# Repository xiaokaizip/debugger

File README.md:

#### 调试器电路

##### 主控（stm32f401rct6）

##### 屏幕（tft屏）

##### 闪存（W25Q32JVSSIQ）

##### 触摸功能（XPT2946）

##### 按键

#### 代码

##### tft屏驱动

- tft屏幕与主控使用spi通讯，然后为了提高屏幕的刷新率，我使用了DMA进行数据的传输。
- tft屏幕的配置更多还是使用网上的库，方便直接。
- 学会更好的使用DMA

##### 触摸功能

- 触摸的功能相对于tft屏幕的驱动来说，是比较好写，但是要完善也还不是很容易，它的功能还需再来研究。

==这两部分可以借鉴老朱的代码（手动狗头），养成写注释的习惯，等到功能写出来再来整理到readme中==

# Debegger

## 代码的设计

### tft屏幕显示

- spi的配置，如下图：（然后再开启个DMA就可以了）

- 屏幕的初始化还是使用普通的方法对其进行初始化（那些初始化的指令还没去了解）。

- 首先是屏幕的设计，目前的想法是，先将一整个屏幕的数据处理完，再使用DMA传输一次性完成传输。（已完成）

- 先将要处理的像素点存储到数组中

~~~c
volatile unsigned char lcd_buffer[128 * 160 * 2] = {0};

~~~

然后直接使用DMA将数据传输到ftf屏中

~~~c
    HAL_SPI_Transmit_DMA(&hspi3, (uint8_t *) lcd_buffer, 128 * 160 * 2);
~~~

- 然后就是对数组的处理了，每一个数组对应tft屏中的一个像素点，所以在处理时，只需将对应的像素点输入对应的颜色指令即可。
  - 在此代码中对应的字符大小为12*6，即宽为6像素，高为12像素。
  - 处理字符时，先从行开始处理的，依次向下处理。
  - 至于其他的方框，就是直接抄袭老朱的代码。（还需待我看懂）

### 串口数据的处理

##### 配置

- 首先是串口的接口，在本调试器中，使用的串口是USART1和UART4

  - usart1：typeC接口，具有usb2ttl芯片

    PA10->RX

    PA9->TX

  - uart4：使用的是gh1.25的接口。

    PC10->TX

    PC11->RX

- 发送数据的时候，还是用了轮询模式。接收数据的时候，使用的是中断模式。

##### 数据类型转换

- 串口传输的是8位的数，所以如果要传输更长的数据类型，需要转换一下数据的类型。在本例程中要传输的是float的数据，所以float和unsigned short 两种类型的数据相互转换。

- 将float转换为unsigned short

  ~~~c
  unsigned short FloatToInt16(float data0)
  ~~~

- 将unsigned short转换为float

  ~~~c
  float Int16ToFloat(unsigned short data0)
  
  ~~~

##### 传输格式

- 目前暂定传输和接收4个float类型数据（这四个数据分别为data1、data2、data3、data4）。使用长度为11的数据。

| 0    | 1    | 2    | 3    | 4    | 5    | 6    | 7    | 8    | 9      | 10   |
| ---- | ---- | ---- | ---- | ---- | ---- | ---- | ---- | ---- | ------ | ---- |
| 0xff | 高位 | 低位 | 高位 | 低位 | 高位 | 低位 | 高位 | 低位 | 校准位 | 0xff |

- 第零位为起始位，指定为0xff，低十位为结束位，指定为0xff。
- 第1位是data1的高8位，第2位是data1低8位。其他的以此类推。
- 第9位是校准位，其实起这个名字可能不太合适，这一位的作用就是用来表示接收了多少个有效数据（非零数据）

## 图形界面的设计

### 现阶段流程图

- 在每一个界面中都有一个TurnBuck选项（除了main_forms界面），按下此界面就会回到上一个界面。这个回调的方法不知是要不要使用链表（有待思考）。

- 图形界面只是使用了按键（Button）以及标签（label）来设计的简易界面。Key1用来移动光标，Key2用来确定进入相依的界面，并使用回调函数还进行初始化，配合链表可能会有更好的效果。

### 设计思路

- key1为选择键，当key1按下时key_Select_flag++；同时相应的button将会高亮表示被选择到。
- 当按下key2时，为确定按键。此时key_Verify_flag=1。此时将会根据key_Select_flag的值调用 相应 的回调函数 进入相应的界面。然后key_Verify_flag被重新置零。
- 此流程是相对较简单的。后面的想法是使用链表来实现界面的切换 。

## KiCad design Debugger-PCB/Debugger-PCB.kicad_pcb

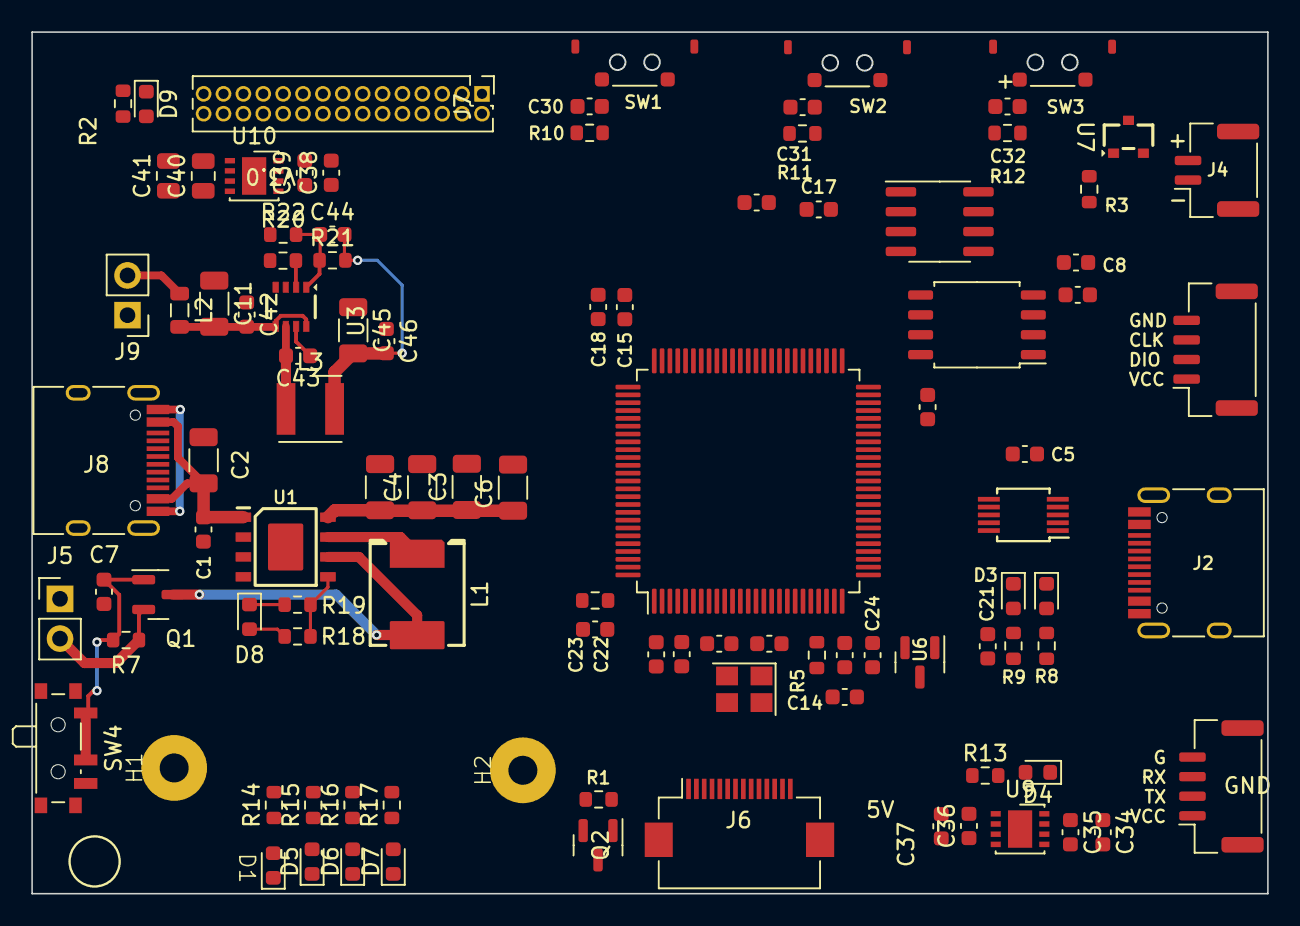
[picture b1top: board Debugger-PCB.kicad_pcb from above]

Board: 2 copper layers, 78.9 x 55.0 mm, 102 parts (0 on the bottom side), 86 nets.

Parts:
C1, C5, C7, C8, C9, C14, C17, C18, C19, C20, C21, C22, C23, C24, C30, C31, C32, C33, C35, C37, C39, C42: 100n; C_0603_1608Metric
C2: 10u; C_1206_3216Metric
C3, C4, C6, C10: 22u; C_1206_3216Metric
C11: 106 1206; C_1206_3216Metric
C12, C13: 12p; C_0603_1608Metric
C15, C16: 2.2u; C_0603_1608Metric
C34, C36, C38: 4.7u; C_0603_1608Metric
C40: 4.7u; C_0805_2012Metric
C41: 100n; C_0805_2012Metric
C43: 103; C_0603_1608Metric
C44: 101; C_0603_1608Metric
C45: 22uf 0603; C_1206_3216Metric
C46: 104; C_0603_1608Metric
D1, D5, D6, D7, D8: LED_0603_1608Metric
D2, D3, D4, D9: LED; LED_0603_1608Metric
H1, H2: MountingHole; mo
J1, J3: Conn_01x04; JST_GH_SM04B-GHS-TB_1x04-1MP_P1.25mm_Horizontal
J2, J8: USB_C_Receptacle_USB2.0; USB_C_Receptacle_HRO_TYPE-C-31-M-12
J4: Conn_01x02; JST_GH_SM02B-GHS-TB_1x02-1MP_P1.25mm_Horizontal
J5, J9: Conn_01x02; PinHeader_1x02_P2.54mm_Vertical
J6: Conn_01x14; Hirose_FH12-14S-0.5SH_1x14-1MP_P0.50mm_Horizontal
J7: axt430124; PinHeader_2x15_P1.27mm_Vertical
L1: 1u; MC-0630
L2: 600r; L_0805_2012Metric
L3: 2.2uh; L_Wurth_WE-LQSH-4020
Q1: AO3407; SOT-23
Q2: SI2301; SOT-23
R1, R6: 10K; R_0603_1608Metric
R2, R13: 1K; R_0603_1608Metric
R3: 120; R_0603_1608Metric
R5, R7, R14, R15, R16, R17, R18, R19: 10k; R_0603_1608Metric
R8, R9, R10, R11, R12: 1k; R_0603_1608Metric
R20: 200K; R_0603_1608Metric
R21: 220K; R_0603_1608Metric
R22: 30k; R_0603_1608Metric
SW1, SW2, SW3: SW_Push; button
SW4: SW_SPDT; SW_SPDT_PCM12
U1: IP5306; SOP-8EP_3949
U2: CH340E; MSOP-10_3x3mm_P0.5mm
U3: SY8303; SOT-23-8
U4: TJA1051T-3; SOIC-8_3.9x4.9mm_P1.27mm
U5: STM32F407VETx; LQFP-100_14x14mm_P0.5mm
U6: REF3030; SOT-23
U7: pesd1can; SOT-23
U8: W25Q32JVSS; SOIC-8_5.23x5.23mm_P1.27mm
U9, U10: DFN-8-1EP_3x3mm_P0.65mm_EP1.55x2.4mm
Y1: 12M; Crystal_SMD_3225-4Pin_3.2x2.5mm

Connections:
+5V: C3.1, C4.1, C6.1, C9.1, C10.1, C34.2, C35.2, C38.2, C39.2, C44.2, C45.2, C46.2, J2.A4 (VBUS), J2.A9 (VBUS), J2.B4 (VBUS), J2.B9 (VBUS), J7.30, L3.2, R21.2, U1.8 (VOUT), U4.3 (VCC), U9.5 (EN), U9.8 (IN), U10.5 (EN), U10.8 (IN)
/Flash/SPI2_CS: U5.51 (PB12), U8.1 (~CS)
/Flash/SPI2_MISO: U5.53 (PB14), U8.2 (DO(IO1))
/Flash/SPI2_MOSI: U5.54 (PB15), U8.5 (DI(IO0))
/Flash/SPI2_SCK: U5.52 (PB13), U8.6 (CLK)
/Key&LED/KEY1: C30.1, J6.8, R10.2, SW1.2, U5.37 (PB2)
/Key&LED/KEY2: C31.1, J6.9, R11.2, SW2.2, U5.36 (PB1)
/Key&LED/KEY3: C32.1, J6.10, R12.2, SW3.2, U5.35 (PB0)
/Key&LED/LED1: D2.1 (K), U5.39 (PE8)
/Key&LED/LED2: D3.1 (K), U5.38 (PE7)
/MCU/ADC1_IN0: J7.25, U5.23 (PA0)
/MCU/ADC1_IN1: J7.24, U5.24 (PA1)
/MCU/ADC1_IN11: J7.29, U5.16 (PC1)
/MCU/ADC1_IN12: J7.28, U5.17 (PC2)
/MCU/ADC1_IN13: J7.27, U5.18 (PC3)
/MCU/ADC1_IN14: J7.26, U5.33 (PC4)
/MCU/CAN_RX: U4.4 (RXD), U5.70 (PA11)
/MCU/CAN_TX: U4.1 (TXD), U5.71 (PA12)
/MCU/I2C3_SCL: J7.13, U5.67 (PA8)
/MCU/I2C3_SDA: J7.14, U5.56 (PD9)
/MCU/KEY4: J6.11, U5.69 (PA10)
/MCU/KEY5: J6.12, U5.68 (PA9)
/MCU/LCD_A0: J7.3, U5.90 (PB4)
/MCU/LCD_CLK: J6.3, J7.5, U5.89 (PB3)
/MCU/LCD_CS: J7.6, U5.77 (PA15), U5.95 (PB8)
/MCU/LCD_CS0: J6.7, U5.15 (PC0)
/MCU/LCD_DC: J6.6, U5.96 (PB9)
/MCU/LCD_LED: J7.7, Q2.1 (G), R1.1, U5.93 (PB7)
/MCU/LCD_MOSI: J6.4, J7.4, U5.91 (PB5)
/MCU/LCD_RST: J6.5, J7.2, U5.92 (PB6)
/MCU/MCU_RXD: U2.8 (TXD), U5.48 (PB11)
/MCU/MCU_TXD: U2.9 (RXD), U5.47 (PB10)
/MCU/OSC_IN: C13.1, U5.12 (PH0), Y1.3
/MCU/OSC_OUT: C12.1, U5.13 (PH1), Y1.1
/MCU/RESET: C14.2, J6.14, R5.2, U5.14 (NRST)
/MCU/RXD: J1.3, U5.26 (PA3)
/MCU/SWCLK: J3.3, U5.76 (PA14)
/MCU/SWDIO: J3.2, U5.72 (PA13)
/MCU/TIM1_CH1: J7.18, U5.40 (PE9)
/MCU/TIM1_CH2: J7.19, U5.42 (PE11)
/MCU/TIM3_CH1: J7.23, U5.63 (PC6)
/MCU/TIM3_CH2: J7.22, U5.64 (PC7)
/MCU/TIM4_CH1: J7.21, U5.60 (PD13)
/MCU/TIM4_CH2: J7.20, U5.59 (PD12)
/MCU/TOUCH_CLK: J7.8, U5.30 (PA5)
/MCU/TOUCH_CS: J7.12, U5.29 (PA4)
/MCU/TOUCH_INT: J7.11, U5.34 (PC5)
/MCU/TOUCH_MISO: J7.9, U5.31 (PA6)
/MCU/TOUCH_MOSI: J7.10, U5.32 (PA7)
/MCU/TXD: J1.2, U5.25 (PA2)
/MCU/VREF: U5.21 (VREF+), U6.2 (OUT)
/Power&Port/CAN+: J4.2, R3.1, U4.7 (CANH), U7.1 (Vin)
/Power&Port/CAN-: J4.1, R3.2, U4.6 (CANL), U7.2 (Vout)
/Power&Port/DN: J2.A7 (D-), J2.B7 (D-), U2.2 (UD-)
/Power&Port/DP: J2.A6 (D+), J2.B6 (D+), U2.1 (UD+)
/Power&Port/VBAT: L1.2, Q1.3 (D), U1.6 (BAT)
/Power&Port/VBAT+: J5.2, Q1.2 (S), R7.2
BATE_5V: C1.2, C2.2, J8.A4 (VBUS), J8.A9 (VBUS), J8.B4 (VBUS), J8.B9 (VBUS), U1.1 (VIN)
G: C7.1, Q1.1 (G), R7.1, SW4.1 (A), SW4.2 (B)
GND: C1.1, C2.1, C5.2, C7.2, C8.2, C9.2, C11.1, C12.2, C13.2, C14.1, C15.1, C16.1, C17.2, C18.2, C19.2, C20.2, C21.2, C22.2, C23.2, C24.2, C30.2, C31.2, C32.2, C33.2, C34.1, C35.1, C36.1, C37.1, C38.1, C39.1, C40.1, C41.1, C42.1, C45.1, C46.1, D4.1 (K), D8.1 (Cathode), D9.1 (K), J1.4, J2.A1 (GND), J2.A12 (GND), J2.B1 (GND), J2.B12 (GND), J2.S1 (SHIELD), J3.4, J5.1, J6.1, J7.15, J7.16, J7.17, J8.A1 (GND), J8.A12 (GND), J8.B1 (GND), J8.B12 (GND), J8.S1 (SHIELD), R1.2, R6.1, R19.1, R20.2, R22.1, SW1.1, SW2.1, SW3.1, SW4.3 (C), U1.EP (GND), U2.3 (GND), U3.3 (GND), U3.4 (GND), U4.2 (GND), U4.8 (S), U5.10 (VSS), U5.20 (VSSA), U5.27 (VSS), U5.74 (VSS), U5.99 (VSS), U6.3 (GND), U7.3 (GND), U8.3 (IO2), U8.4 (GND), U9.4 (GND), U9.9 (GND), U10.4 (GND), U10.9 (GND), Y1.2, Y1.4
GND1: C3.2, C4.2, C6.2, C10.2, J9.1
LCD_3V3: C40.2, C41.2, J7.1, Q2.2 (S), U10.1 (OUT)
unnamed: D1.2 (Anode), R14.1
unnamed: D1.1 (Cathode), D5.2 (Anode), D6.1 (Cathode), D7.2 (Anode), U1.4 (LED3)
unnamed: D2.2 (A), R8.2
unnamed: D3.2 (A), R9.2
unnamed: D4.2 (A), R13.2
unnamed: D5.1 (Cathode), R15.1
unnamed: D6.2 (Anode), R16.1
unnamed: D7.1 (Cathode), R17.1
unnamed: D8.2 (Anode), R18.1
unnamed: D9.2 (A), R2.2
unnamed: J6.2, Q2.3 (D)
unnamed: R18.2, R19.2, U1.5 (KEY)
unnamed: R14.2, R15.2, U1.2 (LED1)
unnamed: R16.2, R17.2, U1.3 (LED2)
unnamed: L1.1, U1.7 (SW)
unnamed: C43.1, U3.7 (BST)
unnamed: C11.2, C42.2, L2.2, U3.5 (VIN), U3.8 (EN)
unnamed: C44.1, R21.1, R22.2, U3.1 (FB)
unnamed: R20.1, U3.2 (FS)
unnamed: C43.2, L3.1, U3.6 (SW)
unnamed: R6.2, U5.94 (BOOT0)
unnamed: C16.2, U5.49 (VCAP_1)
unnamed: C15.2, U5.73 (VCAP_2)
VCC: C5.1, C8.1, C17.1, C18.1, C19.1, C20.1, C21.1, C22.1, C23.1, C24.1, C33.1, C36.2, C37.2, J1.1, J3.1, J9.2, L2.1, R2.1, R5.1, R8.1, R9.1, R10.1, R11.1, R12.1, R13.1, U2.7 (VCC), U2.10 (V3), U4.5 (VIO), U5.6 (VBAT), U5.11 (VDD), U5.19 (VDD), U5.22 (VDDA), U5.28 (VDD), U5.50 (VDD), U5.75 (VDD), U5.100 (VDD), U6.1 (IN), U8.7 (IO3), U8.8 (VCC), U9.1 (OUT)

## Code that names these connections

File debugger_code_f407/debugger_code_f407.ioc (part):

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Mcu.Name=STM32F407V(E-G)Tx
Mcu.Package=LQFP100
Mcu.UserName=STM32F407VETx
PA11.GPIOParameters=GPIO_Label
PA11.GPIO_Label=CAN_RX
PA11.Mode=CAN_Activate
PA11.Signal=CAN1_RX
PA12.GPIOParameters=GPIO_Label
PA12.GPIO_Label=CAN_TX
PA12.Mode=CAN_Activate
PA12.Signal=CAN1_TX
PA13.Mode=Serial_Wire
PA13.Signal=SYS_JTMS-SWDIO
PA14.Mode=Serial_Wire
PA14.Signal=SYS_JTCK-SWCLK
PA15.GPIOParameters=GPIO_Label
PA15.GPIO_Label=LCD_CS
PA15.Mode=NSS_Signal_Hard_Output
PA15.Signal=SPI3_NSS
PA2.GPIOParameters=GPIO_Label
PA2.GPIO_Label=TXD
PA2.Mode=Asynchronous
PA2.Signal=USART2_TX
PA3.GPIOParameters=GPIO_Label
PA3.GPIO_Label=RXD
PA3.Mode=Asynchronous
PA3.Signal=USART2_RX
PA4.GPIOParameters=GPIO_Label
PA4.GPIO_Label=TOUCH_CS
PA4.Mode=NSS_Signal_Hard_Input
PA4.Signal=SPI1_NSS
PA5.GPIOParameters=GPIO_Label
PA5.GPIO_Label=TOUCH_CLK
PA5.Mode=Full_Duplex_Master
PA5.Signal=SPI1_SCK
PA6.GPIOParameters=GPIO_Label
PA6.GPIO_Label=TOUCH_MISO
PA6.Mode=Full_Duplex_Master
PA6.Signal=SPI1_MISO
PA7.GPIOParameters=GPIO_Label
PA7.GPIO_Label=TOUCH_MOSI
PA7.Mode=Full_Duplex_Master
PA7.Signal=SPI1_MOSI
PB0.Signal=GPIO_Input
PB1.Signal=GPIO_Input
PB10.GPIOParameters=GPIO_Label
PB10.GPIO_Label=MCU_TXD
PB10.Mode=Asynchronous
PB10.Signal=USART3_TX
PB11.GPIOParameters=GPIO_Label
PB11.GPIO_Label=MCU_RXD
PB11.Mode=Asynchronous
PB11.Signal=USART3_RX
PB12.Mode=NSS_Signal_Hard_Input
PB12.Signal=SPI2_NSS
PB13.Mode=Full_Duplex_Master
PB13.Signal=SPI2_SCK
PB14.Mode=Full_Duplex_Master
PB14.Signal=SPI2_MISO
PB15.Mode=Full_Duplex_Master
PB15.Signal=SPI2_MOSI
PB2.Signal=GPIO_Input
PB3.GPIOParameters=GPIO_Label
PB3.GPIO_Label=LCD_CLK
PB3.Mode=TX_Only_Simplex_Unidirect_Master
PB3.Signal=SPI3_SCK
PB4.GPIOParameters=GPIO_Label
PB4.GPIO_Label=LCD_AO
PB4.Signal=GPIO_Output
PB5.GPIOParameters=GPIO_Label
PB5.GPIO_Label=LCD_MOSI
PB5.Mode=TX_Only_Simplex_Unidirect_Master
PB5.Signal=SPI3_MOSI
PB6.GPIOParameters=GPIO_Label
PB6.GPIO_Label=LCD_RST
PB6.Signal=GPIO_Output
PB7.GPIOParameters=GPIO_Label
PB7.GPIO_Label=LCD_LED
PB7.Signal=GPIO_Output
PC5.GPIOParameters=GPIO_Label
PC5.GPIO_Label=TOUCH_INT
PC5.Signal=GPIO_Output
PE7.GPIOParameters=GPIO_Label
PE7.GPIO_Label=LED1
PE7.Signal=GPIO_Output
PE8.GPIOParameters=GPIO_Label
PE8.GPIO_Label=LED2
PE8.Signal=GPIO_Output
PH0-OSC_IN.Mode=HSE-External-Oscillator
PH0-OSC_IN.Signal=RCC_OSC_IN
PH1-OSC_OUT.Mode=HSE-External-Oscillator
PH1-OSC_OUT.Signal=RCC_OSC_OUT
RCC.HSE_VALUE=12000000
RCC.SYSCLKFreq_VALUE=168000000
RCC.SYSCLKSource=RCC_SYSCLKSOURCE_PLLCLK
board=custom

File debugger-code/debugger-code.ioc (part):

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Mcu.Name=STM32F103R(C-D-E)Tx
Mcu.Package=LQFP64
Mcu.UserName=STM32F103RCTx
PA0-WKUP.Signal=GPIO_Output
PA1.Signal=GPIO_Output
PA10.Mode=Asynchronous
PA10.Signal=USART1_RX
PA13.Mode=Serial_Wire
PA13.Signal=SYS_JTMS-SWDIO
PA14.Mode=Serial_Wire
PA14.Signal=SYS_JTCK-SWCLK
PA15.Mode=NSS_Signal_Hard_Output
PA15.Signal=SPI3_NSS
PA4.Signal=GPIO_Output
PA5.Mode=Full_Duplex_Master
PA5.Signal=SPI1_SCK
PA6.Mode=Full_Duplex_Master
PA6.Signal=SPI1_MISO
PA7.Mode=Full_Duplex_Master
PA7.Signal=SPI1_MOSI
PA9.Mode=Asynchronous
PA9.Signal=USART1_TX
PB1.Signal=GPIO_Input
PB12.Signal=GPIO_Output
PB13.Mode=Full_Duplex_Master
PB13.Signal=SPI2_SCK
PB14.Mode=Full_Duplex_Master
PB14.Signal=SPI2_MISO
PB15.Mode=Full_Duplex_Master
PB15.Signal=SPI2_MOSI
PB2.Signal=GPIO_Input
PB3.Mode=TX_Only_Simplex_Unidirect_Master
PB3.Signal=SPI3_SCK
PB4.GPIOParameters=GPIO_Label
PB4.GPIO_Label=LCD_AO
PB4.Signal=GPIO_Output
PB5.Mode=TX_Only_Simplex_Unidirect_Master
PB5.Signal=SPI3_MOSI
PB6.GPIOParameters=GPIO_Label
PB6.GPIO_Label=LCD_RST
PB6.Signal=GPIO_Output
PB7.Signal=S_TIM4_CH2
PB8.Mode=CAN_Activate
PB8.Signal=CAN_RX
PB9.Mode=CAN_Activate
PB9.Signal=CAN_TX
PC10.Mode=Asynchronous
PC10.Signal=UART4_TX
PC11.Mode=Asynchronous
PC11.Signal=UART4_RX
PC12.Signal=GPIO_Output
PC13-TAMPER-RTC.Signal=GPIO_Output
PC14-OSC32_IN.Signal=GPIO_Output
PD0-OSC_IN.Mode=HSE-External-Oscillator
PD0-OSC_IN.Signal=RCC_OSC_IN
PD1-OSC_OUT.Mode=HSE-External-Oscillator
PD1-OSC_OUT.Signal=RCC_OSC_OUT
RCC.HSE_VALUE=12000000
RCC.SYSCLKFreq_VALUE=72000000
RCC.SYSCLKSource=RCC_SYSCLKSOURCE_PLLCLK
board=custom

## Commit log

2022-11-11 the first commit of pcb and code
2022-11-12 fix some details of PCB
2022-12-07 add gui、forms、devices.Add finsh the forms of main,suscapDebuger ……
2023-01-01 Finish the GUI
2023-01-01 add the readme.md for the gui
2023-01-15 add the gui of usart_forms.and finish transmit and receive of usart.
2023-01-15 Charge the file structure of project.(Actually,it has been charged from last commit.This commit has improved the project.)
2023-03-27 Charge the CAN communication file. Add the motor_forms.c and motor_forms.h to see the motor CAN's id. Add the imu_forms.c and imu_forms.h to see the imu id and datas.
2023-03-27 Add the motor_forms.c and motor_forms.h . Add the imu_forms.c and imu_forms.h
2023-04-04 Added data fusion for IMUs
2023-04-30 change the file name debugger-code into debugger_code_f103. Change the stm32f103rct6 into stm32f407vet6. Add file debugger_code_f407
2023-05-18 commint something useless
2023-05-20 Finish the config of stm32f407vet6 with debugger board.
2023-05-21 Add FreeRtos. Add fifo file from C board into support file folder. Using fifo to receive can datas. Creating data_processing file folder to sort the file of processing data. (All the changes are in d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
2023-05-29 Add some function of fifo with can data
2023-06-06 Try to use fifo to receive the datas of IMU, but fail. Using the forms.c of MM32 which is creating by LaoZhu.
2023-08-29 temp.change the PCB.And change the code.
